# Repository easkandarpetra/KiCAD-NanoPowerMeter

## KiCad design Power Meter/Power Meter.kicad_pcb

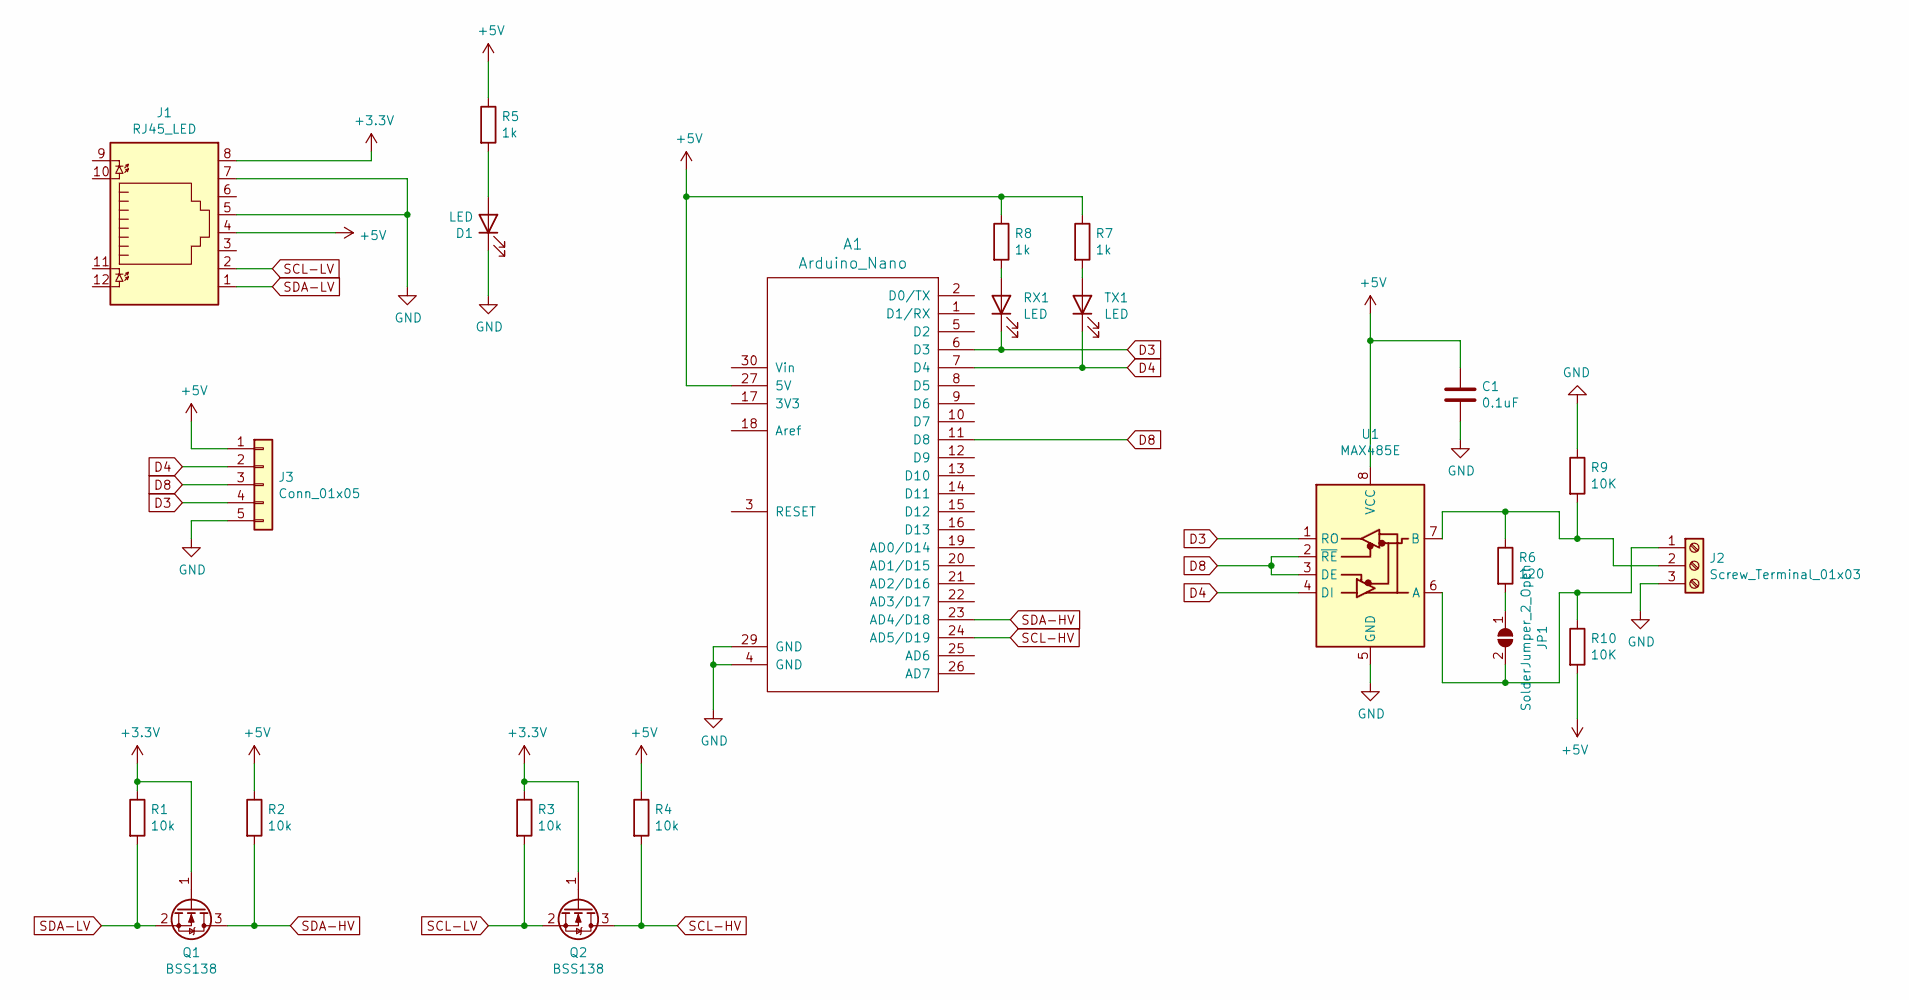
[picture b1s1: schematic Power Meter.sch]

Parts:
A1: Arduino_Nano; arduino_nano2
C1: 0.1uF; C_0805_2012Metric
D1: LED; LED_0805_2012Metric
J1: RJ45_LED; CONNECTOR_RJ45_RA_TH_LEDS
J2: Screw_Terminal_01x03; TerminalBlock_Phoenix_MKDS-1,5-3-5.08_1x03_P5.08mm_Horizont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
J3: Conn_01x05; PinHeader_1x05_P2.54mm_Vertical
JP1: SolderJumper_2_Open; SolderJumper-2_P1.3mm_Open_Pad1.0x1.5mm
Q1, Q2: BSS138; SOT-23
R1, R2, R3, R4: 10k; R_0805_2012Metric
R5, R7, R8: 1k; R_0805_2012Metric
R6: 120; R_0805_2012Metric
R9, R10: 10K; R_0805_2012Metric
RX1: LED; LED_0805_2012Metric
TX1: LED; LED_0805_2012Metric
U1: MAX485E; SOIC-8-1EP_3.9x4.9mm_P1.27mm_EP2.29x3mm

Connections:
+3V3: J1.8, Q1.1 (G), Q2.1 (G), R1.1, R3.1
+5V: A1.27 (5V), C1.1, J1.4, J3.1, R2.1, R4.1, R5.1, R7.1, R8.1, R10.2, U1.8 (VCC)
D3: A1.6 (D3), J3.4, RX1.1 (K), U1.1 (RO)
D4: A1.7 (D4), J3.2, TX1.1 (K), U1.4 (DI)
D8: A1.11 (D8), J3.3, U1.2 (~RE), U1.3 (DE)
GND: A1.4 (GND), A1.29 (GND), C1.2, D1.1 (K), J1.5, J1.7, J2.3, J3.5, R9.1, U1.5 (GND)
unnamed: D1.2 (A), R5.2
unnamed: J2.1, JP1.2 (B), R10.1, U1.6 (A)
unnamed: J2.2, R6.1, R9.2, U1.7 (B)
unnamed: JP1.1 (A), R6.2
unnamed: R7.2, TX1.2 (A)
unnamed: R8.2, RX1.2 (A)
SCL-HV: A1.24 (AD5/D19), Q2.3 (D), R4.2
SCL-LV: J1.2, Q2.2 (S), R3.2
SDA-HV: A1.23 (AD4/D18), Q1.3 (D), R2.2
SDA-LV: J1.1, Q1.2 (S), R1.2

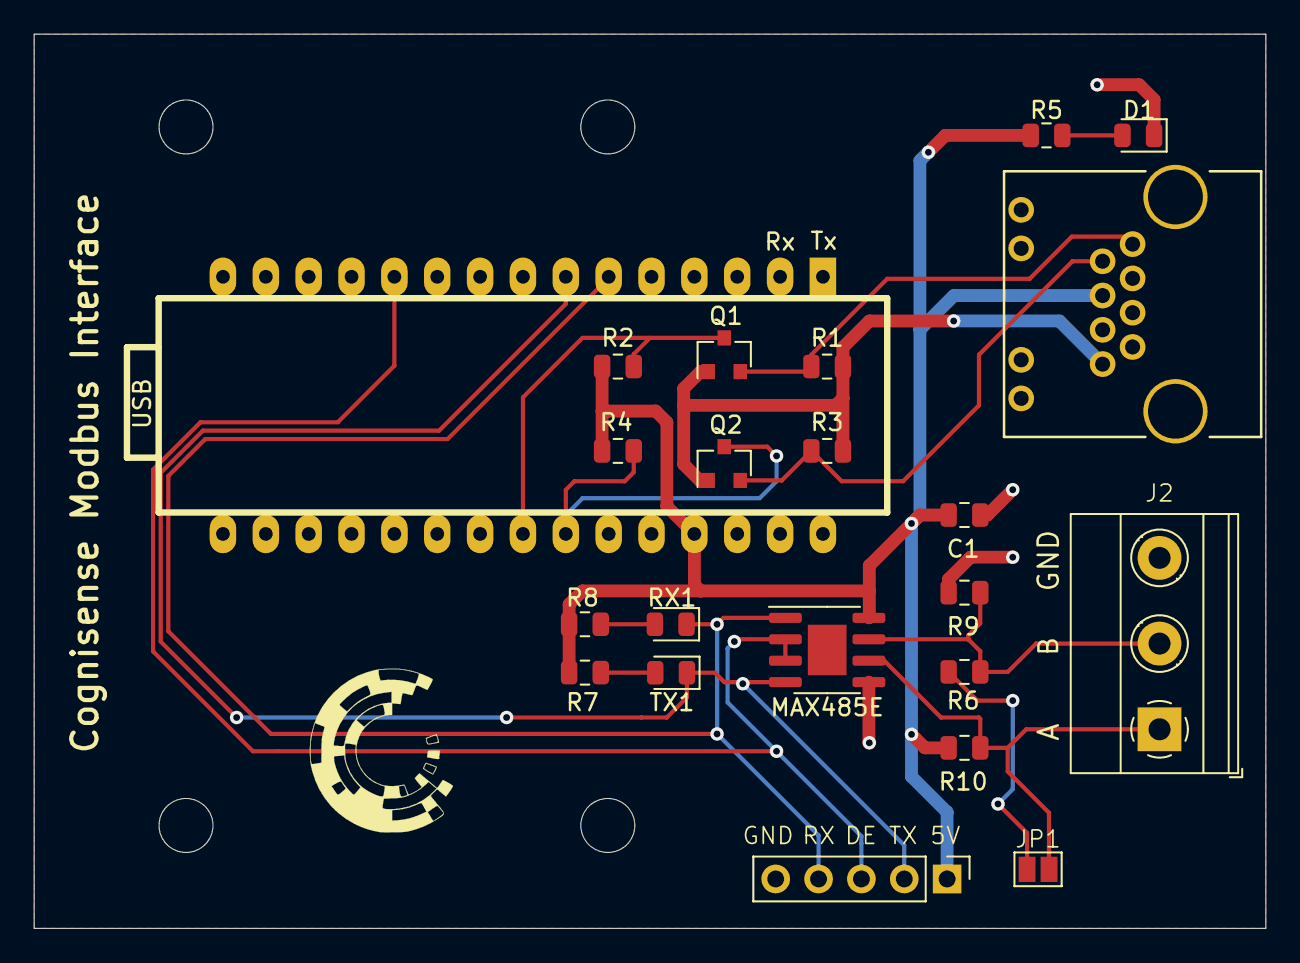
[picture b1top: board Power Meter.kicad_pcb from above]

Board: 2 copper layers, 73.0 x 53.0 mm, 26 parts (0 on the bottom side), 16 nets.

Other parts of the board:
M3, M3#2, M3#3, M3#4: MountingHole_3.2mm_M3

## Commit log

2021-02-28 Edit wire.write()
2021-03-01 Edited the wire.write() data and Wire.requestFrom() line.
